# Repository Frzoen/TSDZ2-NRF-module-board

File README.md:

# TSDZ2 NRF module board

Simple, low component count, inspired by @stsdc

# BOM
| Component | Size | Value |
| --- | --- | --- |
| R1     | 0603 | DNP |
| C1     | 1210 | 2.2uF |
| C2     | 0805 | 22uF |
| Q1     | UDFN6B | SSM6K361NU |
| U1     | NRF Dongle | NRF Dongle |
| U2     | TPSM265R1 | TPSM265R1 |

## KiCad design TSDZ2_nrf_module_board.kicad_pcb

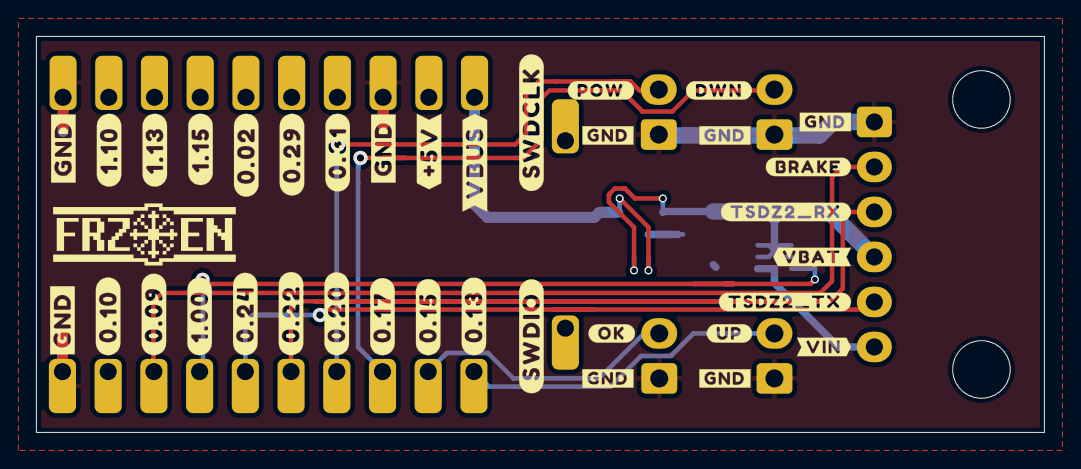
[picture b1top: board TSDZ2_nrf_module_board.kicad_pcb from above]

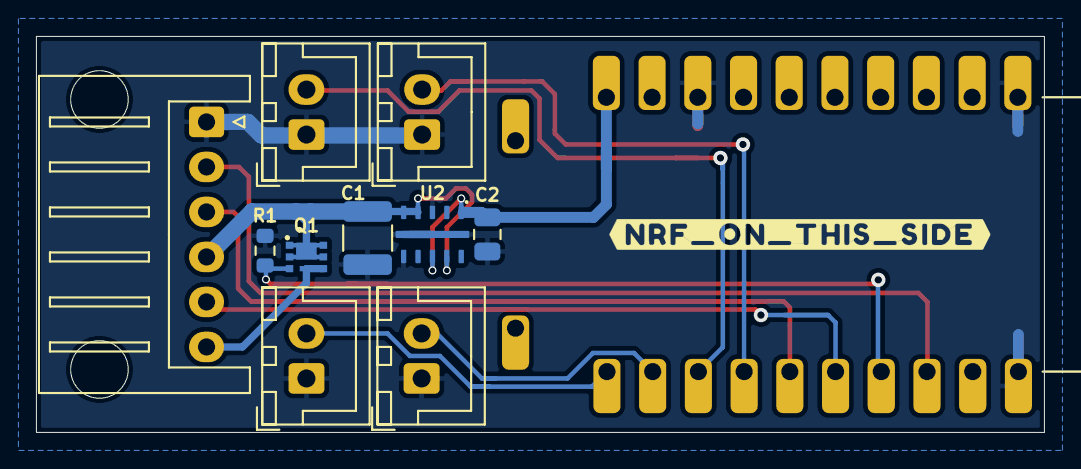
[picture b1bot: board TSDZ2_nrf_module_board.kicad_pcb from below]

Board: 2 copper layers, 56.0 x 22.0 mm, 11 parts (11 on the bottom side), 12 nets.

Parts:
C1: 2.2uF; C_1210_3225Metric
C2: 22uF; C_0805_2012Metric
J1: JST_HX_S6B; JST_XH_S6B-XH-A_1x06_P2.50mm_Horizontal
Q1: SSM6J507NU; UDFN6B
R1: DNP/100KOhm; R_0603_1608Metric
SW1, SW2, SW3, SW4: SW_Push; JST_XH_B2B-XH-A_1x02_P2.50mm_Vertical
U1: NRF52840-DONGLE; MODULE_NRF52840-DONGLE
U2: TPSM265R1

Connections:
/P0.13_UP: SW1.2, U1.0.13
/P0.15_ENTER: SW3.2, U1.0.15
/P0.17_DOWN: SW2.2, U1.0.17
/P0.20_POWER: SW4.2, U1.0.20
/P1.00_VIN_CTRL: Q1.3 (G), R1.1, U1.1.00
/TSDZ2_BRAKE_INPUT: J1.2, U1.0.09
/TSDZ2_RX: J1.3, U1.0.22
/TSDZ2_TX: J1.5, U1.0.24
/TSDZ2_VIN: J1.6, Q1.4 (S), Q1.S
/V_BATT: C1.1, J1.4, Q1.1 (D), Q1.2 (D), Q1.5 (D), Q1.6 (D), Q1.D, U2.4 (VIN), U2.5 (VIN), U2.9 (EN)
GND: C1.2, C2.2, J1.1, R1.2, SW1.1, SW2.1, SW3.1, SW4.1, U1.G1 (GND), U1.G2 (GND), U1.G3 (GND), U2.3 (GND), U2.6 (GND), U2.11 (GND)
VBUS: C2.1, U1.VBUS, U2.1 (VOUT), U2.8 (FB)

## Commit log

2021-02-21 Non chinese version
2021-02-24 Cleanup
2021-02-28 Smol dc/dc
2021-03-03 adawdas
2021-03-04 Awaiting for logo
2021-03-11 Gerbers
2021-03-11 Create LICENSE
